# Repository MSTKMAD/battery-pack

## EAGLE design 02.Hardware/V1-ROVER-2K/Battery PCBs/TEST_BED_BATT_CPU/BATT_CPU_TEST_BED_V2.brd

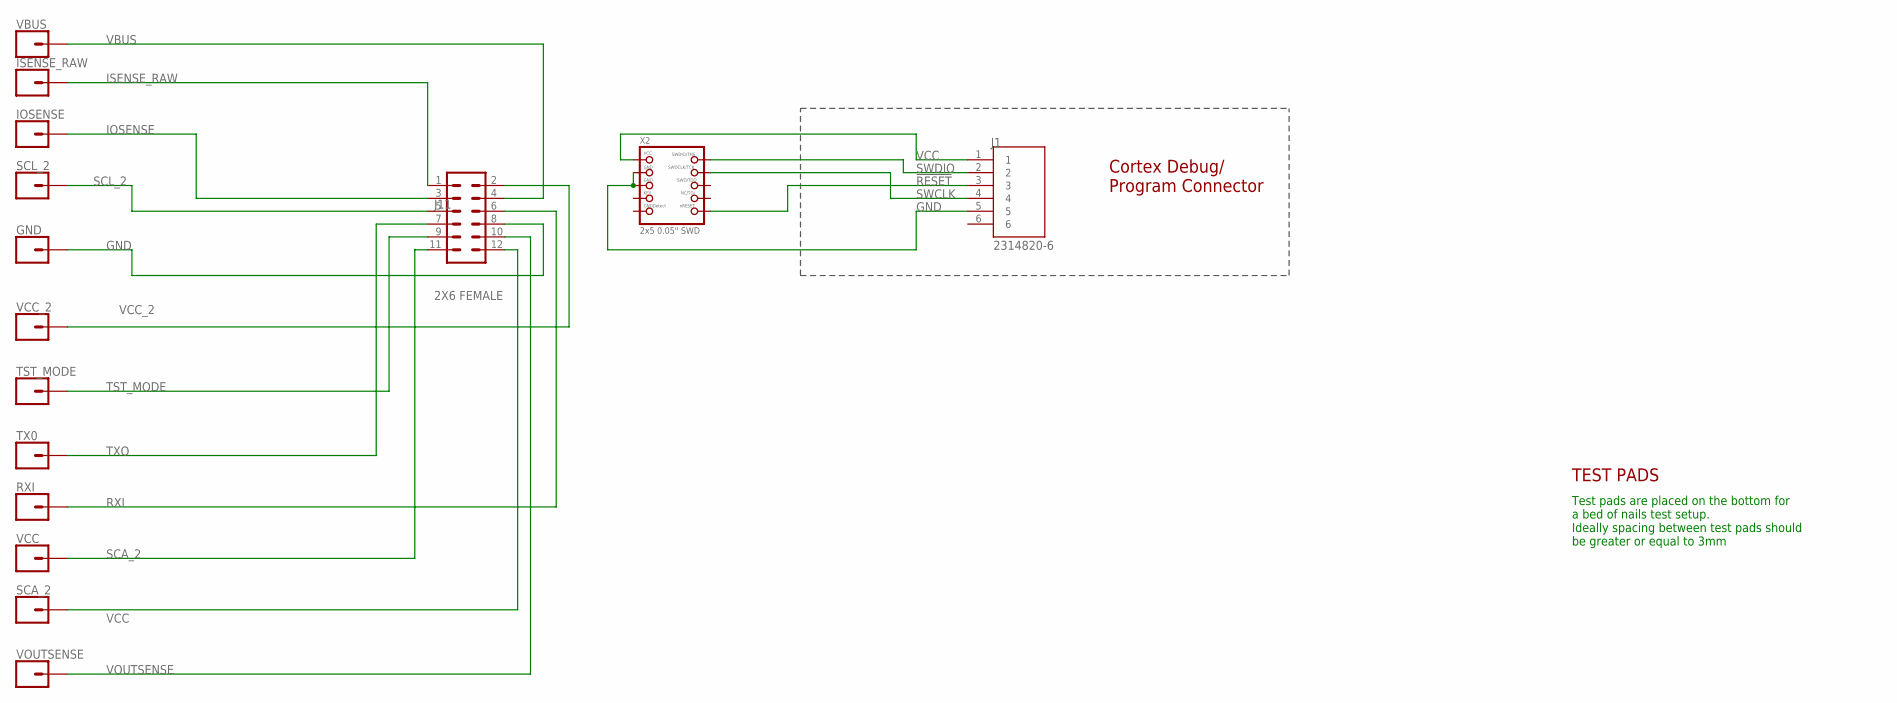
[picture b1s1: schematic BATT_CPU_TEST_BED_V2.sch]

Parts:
GND: CONN_01POGOPIN_HOLE_LARGE; 1X01_POGOPIN_HOLE_0.061_DIA
IOSENSE: CONN_01POGOPIN_HOLE_LARGE; 1X01_POGOPIN_HOLE_0.061_DIA
ISENSE_RAW: CONN_01POGOPIN_HOLE_LARGE; 1X01_POGOPIN_HOLE_0.061_DIA
J1: 2314820-6; TE_2314820-6
J11: 2X6 FEMALE; 2X6
RXI: CONN_01POGOPIN_HOLE_LARGE; 1X01_POGOPIN_HOLE_0.061_DIA
SCA_2: CONN_01POGOPIN_HOLE_LARGE; 1X01_POGOPIN_HOLE_0.061_DIA
SCL_2: CONN_01POGOPIN_HOLE_LARGE; 1X01_POGOPIN_HOLE_0.061_DIA
TST_MODE: CONN_01POGOPIN_HOLE_LARGE; 1X01_POGOPIN_HOLE_0.061_DIA
TX0: CONN_01POGOPIN_HOLE_LARGE; 1X01_POGOPIN_HOLE_0.061_DIA
VBUS: CONN_01POGOPIN_HOLE_LARGE; 1X01_POGOPIN_HOLE_0.061_DIA
VCC: CONN_01POGOPIN_HOLE_LARGE; 1X01_POGOPIN_HOLE_0.061_DIA
VCC_2: CONN_01POGOPIN_HOLE_LARGE; 1X01_POGOPIN_HOLE_0.061_DIA
VOUTSENSE: CONN_01POGOPIN_HOLE_LARGE; 1X01_POGOPIN_HOLE_0.061_DIA
X2: 2x5 0.05" SWD; 2X05_1.27MM_BOX_POSTS

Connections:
!RESET: J1.3, X2.10 (NRESET)
GND: GND.2, J1.5, J11.8, X2.3 (GND), X2.5 (GND)
IOSENSE: IOSENSE.2, J11.3
ISENSE_RAW: ISENSE_RAW.2, J11.1
RXI: J11.6, RXI.2
SCA_2: J11.12, SCA_2.2
SCL_2: J11.5, SCL_2.2
SWCLK: J1.4, X2.4 (SWDCLK)
SWDIO: J1.2, X2.2 (SWDIO)
TST_MODE: J11.9, TST_MODE.2
TXO: J11.7, TX0.2
VBUS: J11.4, VBUS.2
VCC: J1.1, J11.11, VCC.2, X2.1 (VCC)
VCC_2: J11.2, VCC_2.2
VOUTSENSE: J11.10, VOUTSENSE.2

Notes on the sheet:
Cortex Debug/ Program Connector
TEST PADS
Test pads are placed on the bottom for a bed of nails test setup. Ideally spacing between test pads should be greater or equal to 3mm

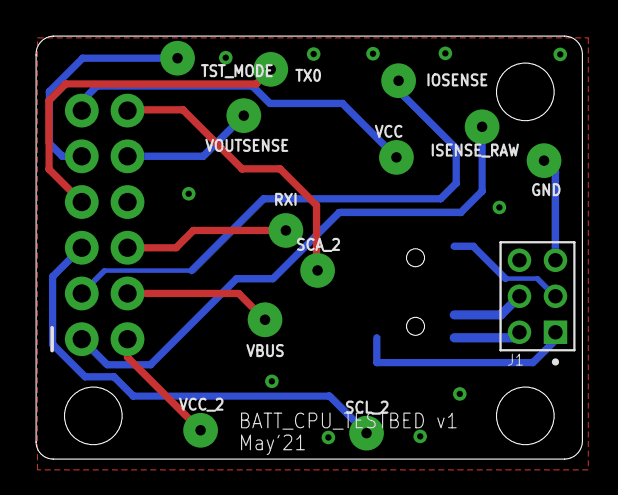
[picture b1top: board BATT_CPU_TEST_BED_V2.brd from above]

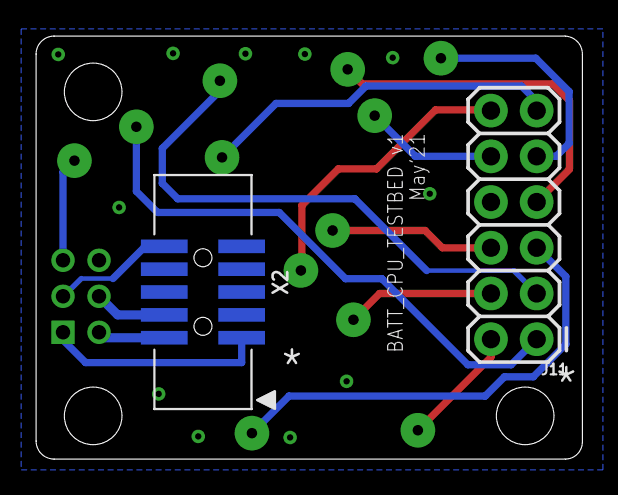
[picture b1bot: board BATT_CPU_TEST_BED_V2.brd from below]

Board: 4 copper layers, 30.4 x 23.5 mm, 15 parts (2 on the bottom side), 15 nets.

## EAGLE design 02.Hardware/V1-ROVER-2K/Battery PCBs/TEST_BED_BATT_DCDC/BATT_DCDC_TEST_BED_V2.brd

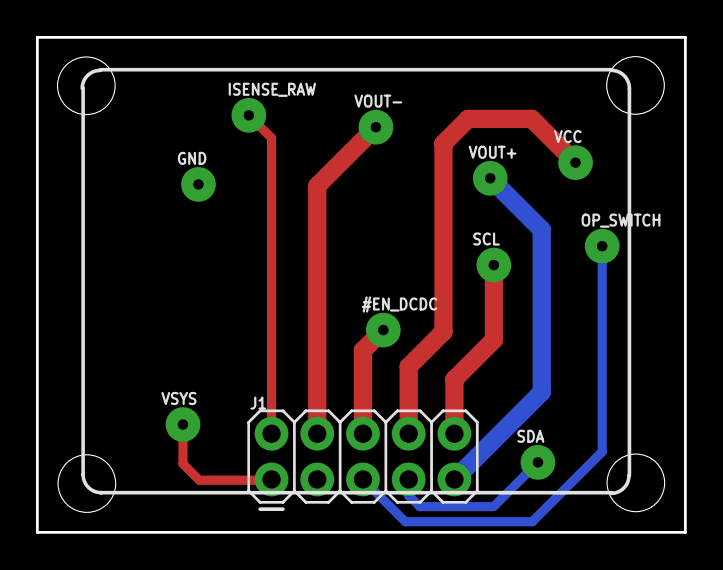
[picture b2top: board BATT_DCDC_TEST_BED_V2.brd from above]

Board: 2 copper layers, 36.0 x 27.5 mm, 11 parts (0 on the bottom side), 10 nets.

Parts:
#EN_DCDC: 1X01_POGOPIN_HOLE_0.061_DIA
GND: 1X01_POGOPIN_HOLE_0.061_DIA
ISENSE_RAW: 1X01_POGOPIN_HOLE_0.061_DIA
J1: 2X5
OP_SWITCH: 1X01_POGOPIN_HOLE_0.061_DIA
SCL: 1X01_POGOPIN_HOLE_0.061_DIA
SDA: 1X01_POGOPIN_HOLE_0.061_DIA
VCC: 1X01_POGOPIN_HOLE_0.061_DIA
VOUT+: 1X01_POGOPIN_HOLE_0.061_DIA
VOUT-: 1X01_POGOPIN_HOLE_0.061_DIA
VSYS: 1X01_POGOPIN_HOLE_0.061_DIA

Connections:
GND: GND.2, J1.3
unnamed: #EN_DCDC.2, J1.6
unnamed: ISENSE_RAW.2, J1.2
unnamed: J1.4, VOUT-.2
unnamed: J1.8, VCC.2
unnamed: J1.10, SCL.2
unnamed: J1.5, OP_SWITCH.2
unnamed: J1.1, VSYS.2
unnamed: J1.7, SDA.2
unnamed: J1.9, VOUT+.2

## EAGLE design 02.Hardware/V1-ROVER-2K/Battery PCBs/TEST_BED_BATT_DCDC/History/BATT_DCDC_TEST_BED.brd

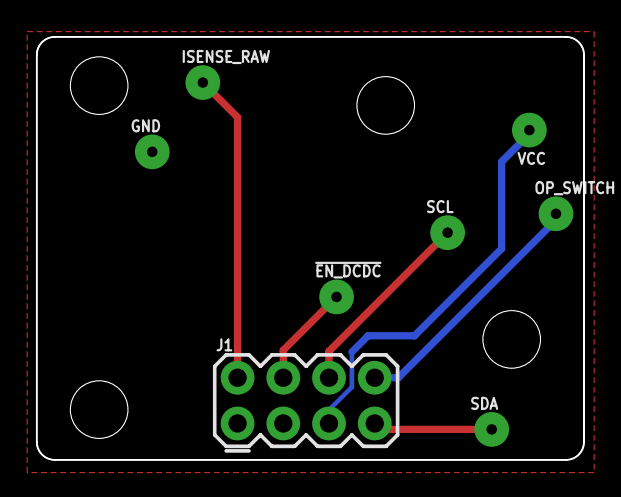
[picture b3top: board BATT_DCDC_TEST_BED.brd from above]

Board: 4 copper layers, 30.4 x 23.5 mm, 8 parts (0 on the bottom side), 7 nets.

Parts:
!EN_DCDC!: 1X01_POGOPIN_HOLE_0.061_DIA
GND: 1X01_POGOPIN_HOLE_0.061_DIA
ISENSE_RAW: 1X01_POGOPIN_HOLE_0.061_DIA
J1: 2X4
OP_SWITCH: 1X01_POGOPIN_HOLE_0.061_DIA
SCL: 1X01_POGOPIN_HOLE_0.061_DIA
SDA: 1X01_POGOPIN_HOLE_0.061_DIA
VCC: 1X01_POGOPIN_HOLE_0.061_DIA

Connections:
EN_DCDC: !EN_DCDC!.2, J1.4
GND: GND.2, J1.1, J1.3
ISENSE_RAW: ISENSE_RAW.2, J1.2
OP_SWITCH: J1.8, OP_SWITCH.2
SCL: J1.6, SCL.2
SDA: J1.7, SDA.2
VCC: J1.5, VCC.2

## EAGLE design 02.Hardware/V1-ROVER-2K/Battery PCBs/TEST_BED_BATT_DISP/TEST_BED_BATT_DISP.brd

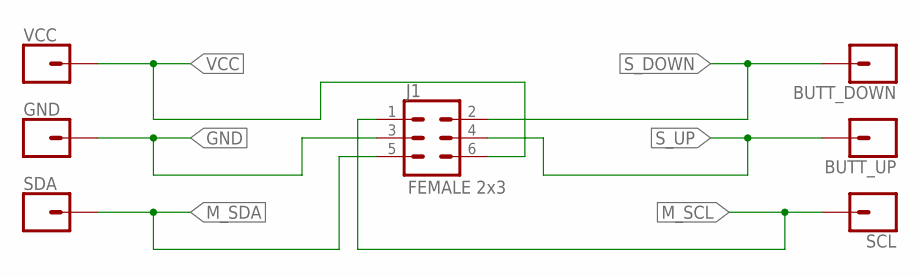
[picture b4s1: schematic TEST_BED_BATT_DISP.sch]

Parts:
BUTT_DOWN: CONN_01POGOPIN_HOLE_LARGE; 1X01_POGOPIN_HOLE_0.061_DIA
BUTT_UP: CONN_01POGOPIN_HOLE_LARGE; 1X01_POGOPIN_HOLE_0.061_DIA
GND: CONN_01POGOPIN_HOLE_LARGE; 1X01_POGOPIN_HOLE_0.061_DIA
J1: FEMALE 2x3; 2X3
SCL: CONN_01POGOPIN_HOLE_LARGE; 1X01_POGOPIN_HOLE_0.061_DIA
SDA: CONN_01POGOPIN_HOLE_LARGE; 1X01_POGOPIN_HOLE_0.061_DIA
VCC: CONN_01POGOPIN_HOLE_LARGE; 1X01_POGOPIN_HOLE_0.061_DIA

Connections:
GND: GND.2, J1.3
M_SCL: J1.1, SCL.2
M_SDA: J1.5, SDA.2
S_DOWN: BUTT_DOWN.2, J1.2
S_UP: BUTT_UP.2, J1.4
VCC: J1.6, VCC.2

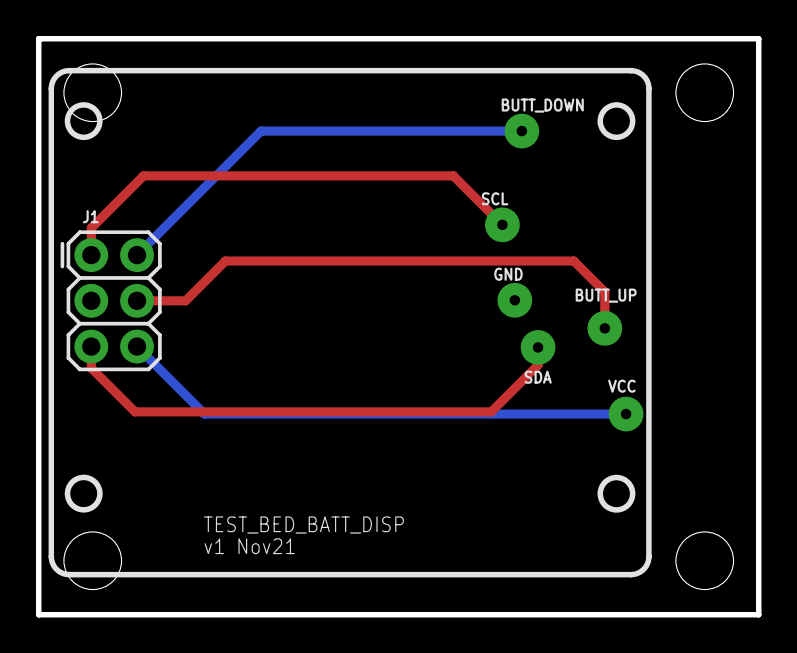
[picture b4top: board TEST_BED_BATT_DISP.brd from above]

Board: 2 copper layers, 40.0 x 32.0 mm, 7 parts (0 on the bottom side), 6 nets.

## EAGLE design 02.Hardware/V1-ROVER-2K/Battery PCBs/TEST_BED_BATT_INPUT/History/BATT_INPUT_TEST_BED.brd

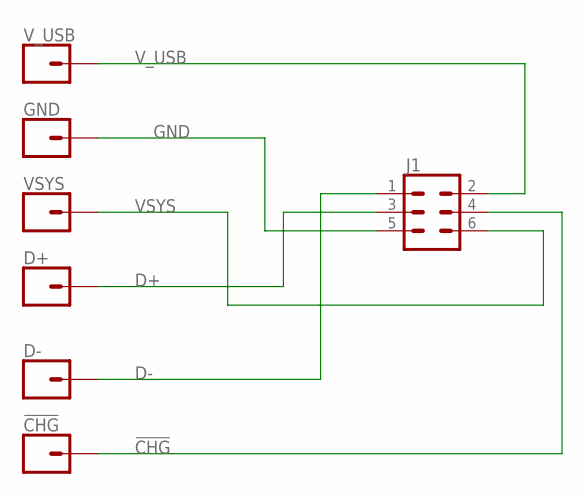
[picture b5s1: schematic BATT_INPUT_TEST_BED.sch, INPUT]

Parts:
!CHG!: CONN_01POGOPIN_HOLE_LARGE; 1X01_POGOPIN_HOLE_0.061_DIA
D+: CONN_01POGOPIN_HOLE_LARGE; 1X01_POGOPIN_HOLE_0.061_DIA
D-: CONN_01POGOPIN_HOLE_LARGE; 1X01_POGOPIN_HOLE_0.061_DIA
GND: CONN_01POGOPIN_HOLE_LARGE; 1X01_POGOPIN_HOLE_0.061_DIA
J1: CONN_03X22X3_SILK_MALE_PTH; 2X3
VSYS: CONN_01POGOPIN_HOLE_LARGE; 1X01_POGOPIN_HOLE_0.061_DIA
V_USB: CONN_01POGOPIN_HOLE_LARGE; 1X01_POGOPIN_HOLE_0.061_DIA

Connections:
!CHG!: !CHG!.2, J1.4
D+: D+.2, J1.3
D-: D-.2, J1.1
GND: GND.2, J1.5
VSYS: J1.6, VSYS.2
V_USB: J1.2, V_USB.2

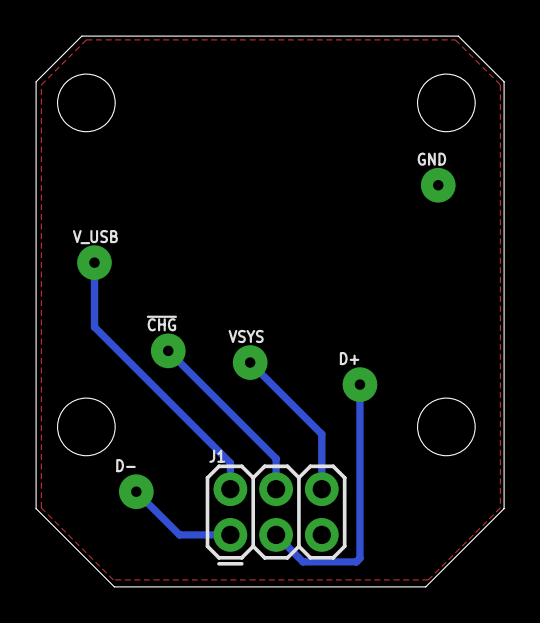
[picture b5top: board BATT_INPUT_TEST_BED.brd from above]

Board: 4 copper layers, 26.0 x 30.6 mm, 7 parts (0 on the bottom side), 6 nets.

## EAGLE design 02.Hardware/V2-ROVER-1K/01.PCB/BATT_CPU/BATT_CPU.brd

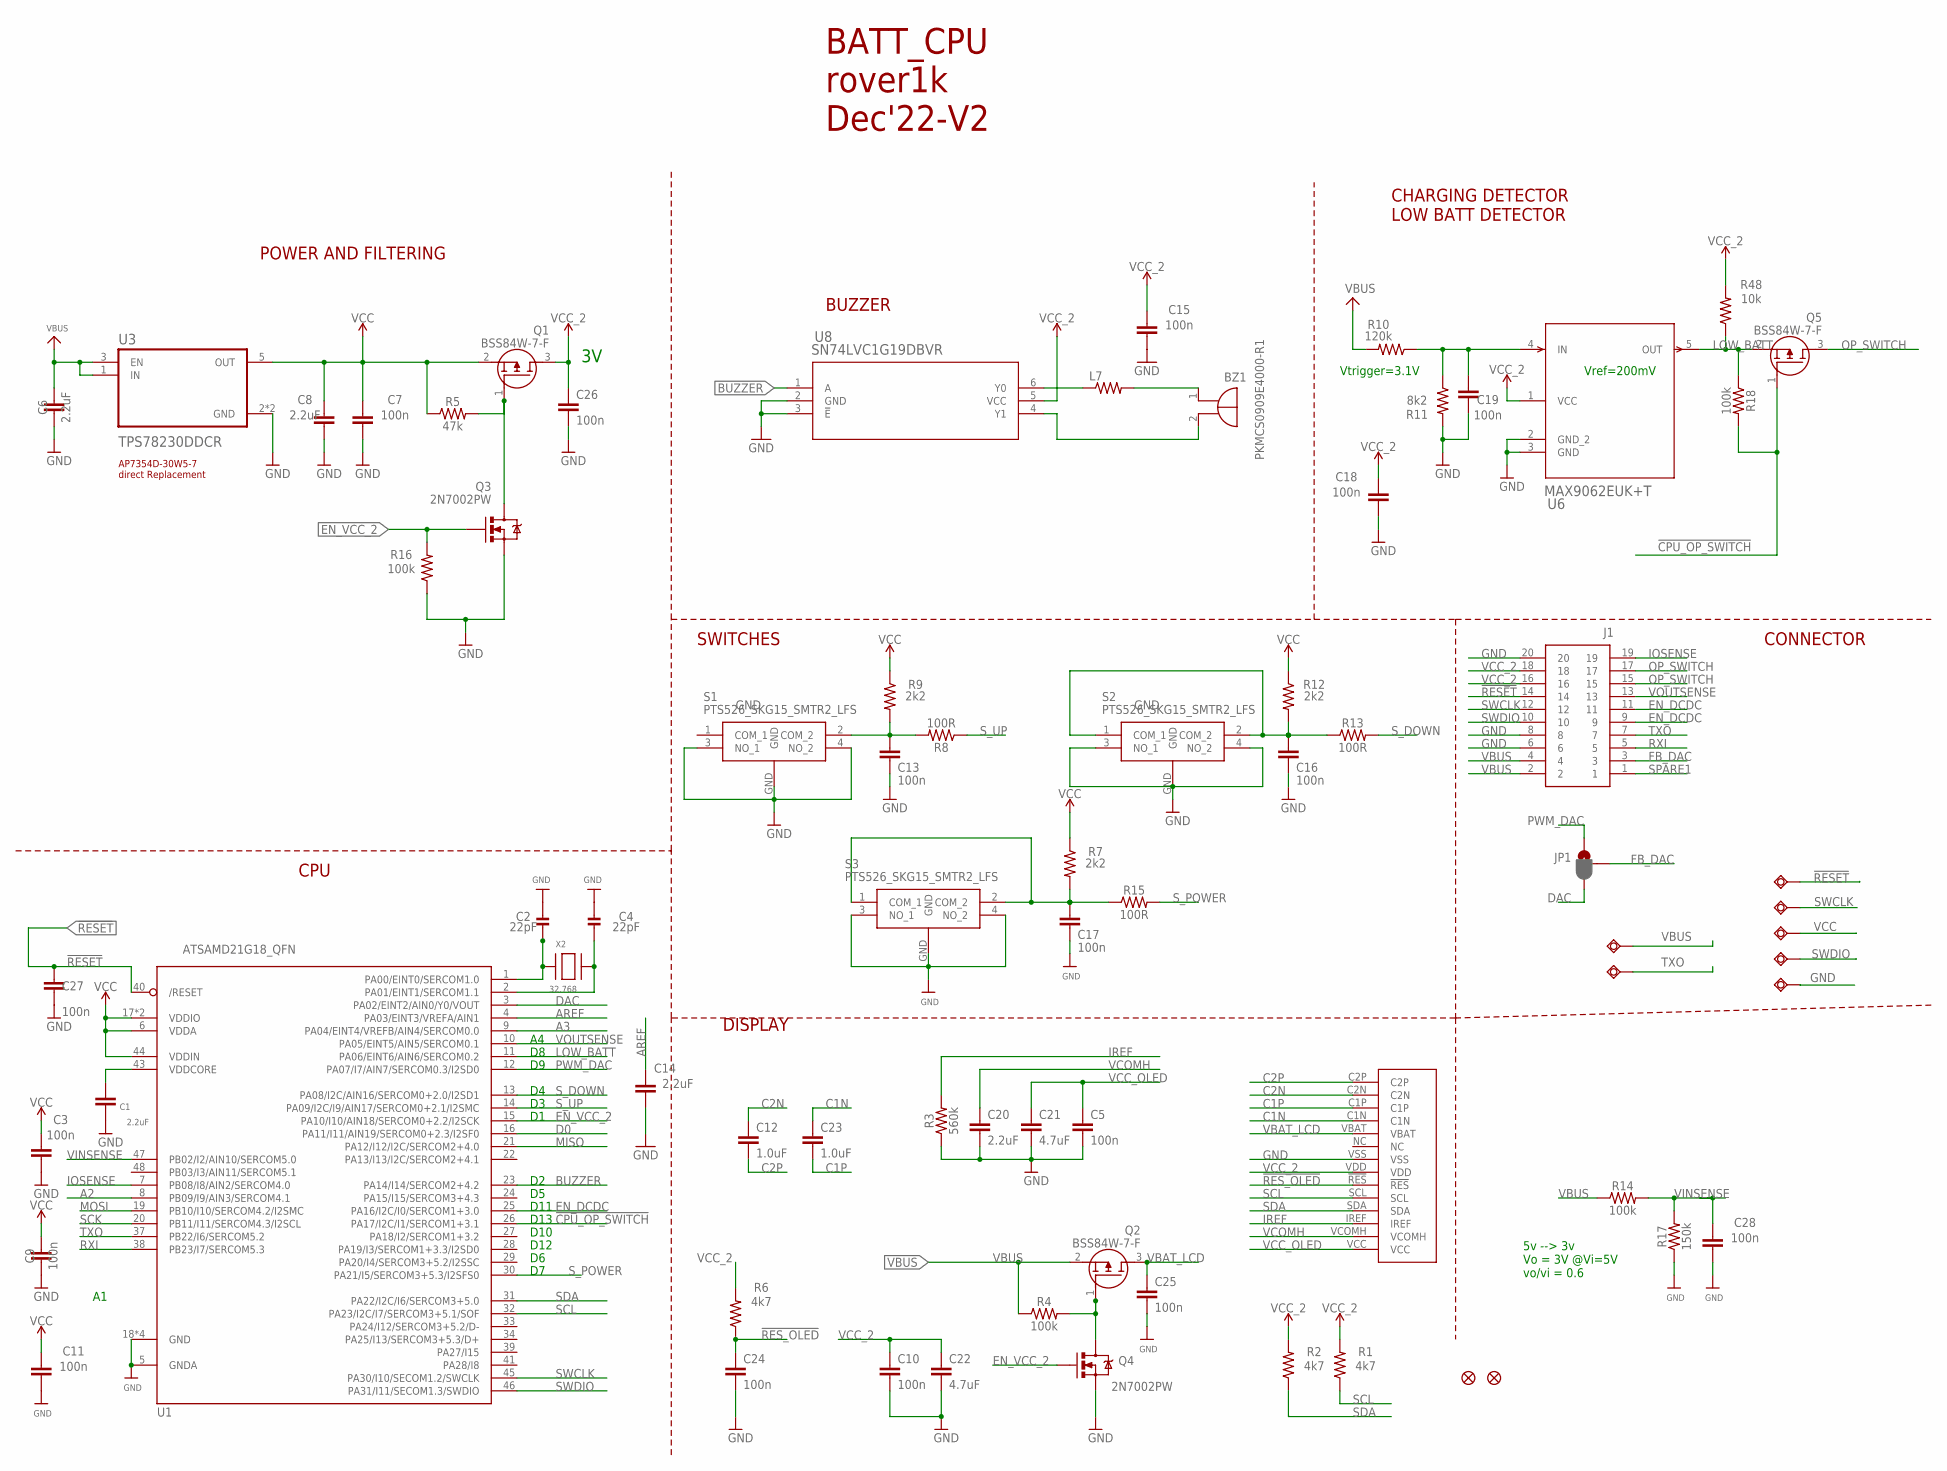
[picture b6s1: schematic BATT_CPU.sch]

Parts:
BZ1: PKMCS0909E4000-R1; PKMCS0909
C1, C6, C8, C14, C20: 2.2uF; 0603
C2, C4: 22pF; 0603-NO
C3, C5, C7, C9, C10, C11, C13, C15, C16, C17, C18, C19, C24, C25, C26, C27, C28: 100n; 0402
C12, C23: 1.0uF; 0402
C21, C22: 4.7uF; 0603
J1: DF40C_2.0_-20DS-0.4V_51_; DF40C2020DS04V51
JP1: JUMPER-SMT_3_1-NC_PASTE_SILK; SMT-JUMPER_3_1-NC_PASTE_SILK
L7: MMZ2012Y202BT000; 0805
Q1, Q2, Q5: BSS84W-7-F; SOT65P222X110-3N
Q3, Q4: 2N7002PW; SOT323
R1, R2, R6: 4k7; 0402
R3: 560k; 0402
R4, R14, R16, R18: 100k; 0402
R5: 47k; 0402
R7, R9, R12: 2k2; 0402
R8, R13, R15: 100R; 0402
R10: 120k; 0402
R11: 8k2; 0402
R17: 150k; 0402
R48: 10k; 0402
S1, S2, S3: PTS526_SKG15_SMTR2_LFS; PTS526SKG15SMTR2LFS
U1: ATSAMD21G18_QFN; TQFN48_7MM
U3: TPS78230DDCR; SOT95P280X110-5N
U6: MAX9062EUK+T; 21-0057F_MXM
U8: SN74LVC1G19DBVR; DBV6
U$30: 64X32_OLED_049; LCD_14_PINS
U$34, U$35: FIDUCIAL""; FIDUCIAL_1MM
VBUS, VBUS1, VBUS2, VBUS3, VBUS4, VBUS5, VBUS6: TESTPAD_TPSQB1,27; TESTPAD_B1,27
X2: 32.768; XTAL3215

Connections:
!CPU_OP_SWITCH: Q5.1 (G), R18.2, U1.26 (PA17/I2C/I1/SERCOM1+3.1)
!RESET: C27.1, J1.14, U1.40 (/RESET), VBUS1.TP
!RES_OLED: C24.1, R6.1, U$30.!RES
A2: U1.8 (PB09/I9/AIN3/SERCOM4.1)
A3: U1.9 (PA04/EINT4/VREFB/AIN4/SERCOM0.0)
AREF: C14.1, U1.4 (PA03/EINT3/VREFA/AIN1)
BUZZER: U1.23 (PA14/I14/SERCOM2+4.2), U8.1 (A)
C1N: C23.1, U$30.C1N
C1P: C23.2, U$30.C1P
C2N: C12.1, U$30.C2N
C2P: C12.2, U$30.C2P
D0: U1.16 (PA11/I11/AIN19/SERCOM0+2.3/I2SF0)
DAC: JP1.3, U1.3 (PA02/EINT2/AIN0/Y0/VOUT)
EN_DCDC: J1.9, J1.11, U1.25 (PA16/I2C/I0/SERCOM1+3.0)
EN_VCC_2: Q3.1 (G), Q4.1 (G), R16.2, U1.15 (PA10/I10/AIN18/SERCOM0+2.2/I2SCK)
FB_DAC: J1.3, JP1.2
GND: C1.2, C2.2, C3.2, C4.2, C5.2, C6.2, C7.2, C8.2, C9.2, C10.2, C11.2, C13.2, C14.2, C15.2, C16.2, C17.2, C18.2, C19.2, C20.2, C21.2, C22.2, C24.2, C25.2, C26.2, C27.2, C28.2, J1.6, J1.8, J1.20, Q3.2 (S), Q4.2 (S), R3.1, R11.2, R16.1, R17.1, S1.3 (NO_1), S1.4 (NO_2), S1.GND, S2.3 (NO_1), S2.4 (NO_2), S2.GND, S3.3 (NO_1), S3.4 (NO_2), S3.GND, U1.5 (GNDA), U1.18 (GND), U1.35 (GND), U1.42 (GND), U1.THERMAL (GND), U3.2 (GND), U3.4 (GND), U6.2 (GND_2), U6.3 (GND), U8.2 (GND), U8.3 (!E), U$30.VSS, VBUS4.TP
IOSENSE: J1.19, U1.7 (PB08/I8/AIN2/SERCOM4.0)
IREF: R3.2, U$30.IREF
LOW_BATT: Q5.2 (S), R18.1, R48.1, U1.11 (PA06/EINT6/AIN6/SERCOM0.2), U6.5 (OUT)
MISO: U1.21 (PA12/I12/I2C/SERCOM2+4.0)
MOSI: U1.19 (PB10/I10/SERCOM4.2/I2SMC)
unnamed: C17.1, R7.2, R15.1, S3.1 (COM_1), S3.2 (COM_2)
unnamed: C13.1, R8.2, R9.2, S1.2 (COM_2)
unnamed: C16.1, R12.2, R13.1, S2.1 (COM_1), S2.2 (COM_2)
unnamed: Q2.1 (G), Q4.3 (D), R4.2
unnamed: C2.1, U1.1 (PA00/EINT0/SERCOM1.0), X2.P$1
unnamed: Q1.1 (G), Q3.3 (D), R5.2
unnamed: C4.1, U1.2 (PA01/EINT1/SERCOM1.1), X2.P$2
unnamed: C19.1, R10.1, R11.1, U6.4 (IN)
unnamed: L7.1, U8.6 (Y0)
unnamed: BZ1.1 (+), L7.2
unnamed: BZ1.2 (-), U8.4 (Y1)
OP_SWITCH: J1.15, J1.17, Q5.3 (D)
PWM_DAC: JP1.1, U1.12 (PA07/I7/AIN7/SERCOM0.3/I2SD0)
RXI: J1.5, U1.38 (PB23/I7/SERCOM5.3)
SCK: U1.20 (PB11/I11/SERCOM4.3/I2SCL)
SCL: R1.1, U1.32 (PA23/I2C/I7/SERCOM3+5.1/SOF), U$30.SCL
SDA: R2.1, U1.31 (PA22/I2C/I6/SERCOM3+5.0), U$30.SDA
SPARE1: J1.1
SWCLK: J1.12, U1.45 (PA30/I10/SECOM1.2/SWCLK), VBUS2.TP
SWDIO: J1.10, U1.46 (PA31/I11/SECOM1.3/SWDIO), VBUS3.TP
S_DOWN: R13.2, U1.13 (PA08/I2C/AIN16/SERCOM0+2.0/I2SD1)
S_POWER: R15.2, U1.30 (PA21/I5/SERCOM3+5.3/I2SFS0)
S_UP: R8.1, U1.14 (PA09/I2C/I9/AIN17/SERCOM0+2.1/I2SMC)
TXO: J1.7, U1.37 (PB22/I6/SERCOM5.2), VBUS6.TP
VBAT_LCD: C25.1, Q2.3 (D), U$30.VBAT
VBUS: C6.1, J1.2, J1.4, Q2.2 (S), R4.1, R10.2, R14.1, U3.1 (IN), U3.3 (EN), VBUS5.TP
VCC: C3.1, C7.1, C8.1, C9.1, C11.1, Q1.2 (S), R5.1, R7.1, R9.1, R12.1, R48.2, U1.6 (VDDA), U1.17 (VDDIO), U1.36 (VDDIO), U1.44 (VDDIN), U3.5 (OUT), VBUS.TP
VCC_2: C10.1, C15.1, C18.1, C22.1, C26.1, J1.16, J1.18, Q1.3 (D), R1.2, R2.2, R6.2, U6.1 (VCC), U8.5 (VCC), U$30.VDD
VCC_OLED: C5.1, C21.1, U$30.VCC
VCOMH: C20.1, U$30.VCOMH
VDDCORE: C1.1, U1.43 (VDDCORE)
VINSENSE: C28.1, R14.2, R17.2, U1.47 (PB02/I2/AIN10/SERCOM5.0)
VOUTSENSE: J1.13, U1.10 (PA05/EINT5/AIN5/SERCOM0.1)

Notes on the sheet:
POWER AND FILTERING
BUZZER
AP7354D-30W5-7 direct Replacement
D10
CHARGING DETECTOR LOW BATT DETECTOR
CPU
Vref=200mV
Vtrigger=3.1V
D13
D11
D12
5v --> 3v Vo = 3V @Vi=5V vo/vi = 0.6
BATT_CPU rover1k Dec'22-V2
DISPLAY
SWITCHES
CONNECTOR

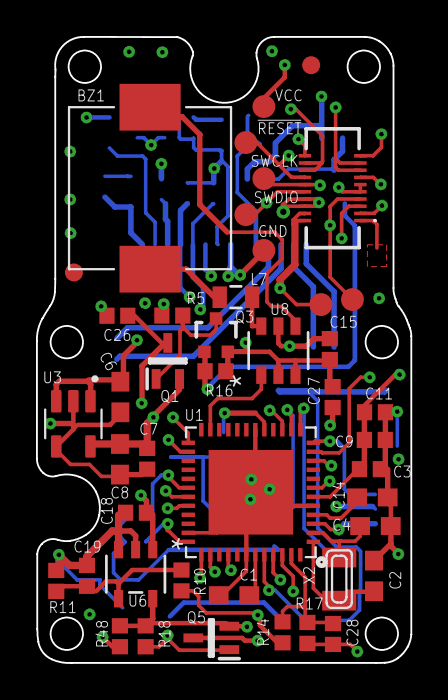
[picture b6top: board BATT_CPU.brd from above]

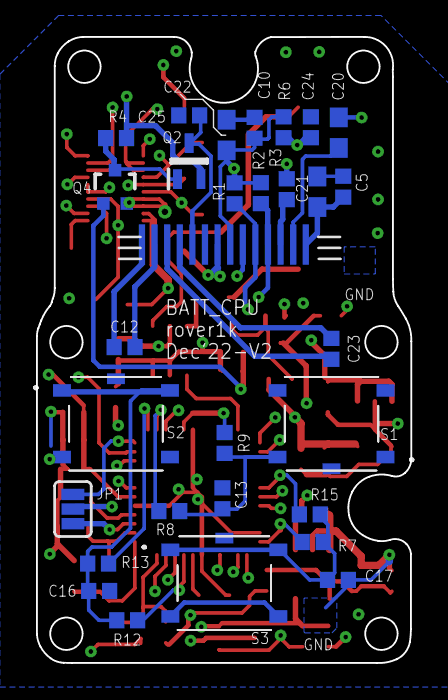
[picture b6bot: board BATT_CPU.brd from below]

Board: 4 copper layers, 20.8 x 34.8 mm, 74 parts (30 on the bottom side), 48 nets.

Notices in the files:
parts and their libraries:
SparkFun-Connectors: Licensing: Creative Commons ShareAlike 4.0 International - https://creativecommons.org/licenses/by-sa/4.0
microbuilder: This work is placed in the public domain, and may be freely used for commercial and non-commercial work with the following conditions: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
